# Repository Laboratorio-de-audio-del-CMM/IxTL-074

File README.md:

# IxTL-074

El IxTL-074 es un sintetizador DIY de frecuencia modulada (FM) desarrollado en el [Laboratorio de Experimentación Sonora del Centro Multimedia](https://www.instagram.com/labaudiocmm) entre agosto y octubre del 2026.

Su nombre proviene de un juego de palabras derivado del nombre de la fibra vegetal extraída de algunas especies de maguey (Ixtle[^1]) y uno de los componentes del sintetizador (el amplificador operacional TL-074). Busca trazar un paralelismo entre el tejido material de fibras vegetales y el sonido derivado de las interconexiones entre operadores de la síntesis FM.

## Funcionamiento
El IxTL-074 se compone de cuatro osciladores de onda cuadrada, cada uno con un rango de oscilación dedicado:

* **Oscilador 1:** 1.7 - 140 Hz aproximadamente
* **Oscilador 2:** 6.5 - 463 Hz aproximadamente
* **Oscilador 3:** 137 - 2266 Hz aproximadamente
* **Oscilador 4:** 147 - 5848 Hz aproximadamente

La frecuencia y amplitud de cada oscilador son determinadas por controles dedicados. La frecuencia puede ser variada mediante una señal moduladora [^2].

Cada oscilador cuenta con:
* **Tres salidas:**
    
    Correspondientes a la frecuencia y a la amplitud establecida con los controles dedicados. Cada salida puede funcionar como:
    * señal de audio, al conectarse a la mezcladora integrada
    * señal moduladora, al conectarse a las entradas de otro oscilador, o a su propia entrada

* **Tres entradas**

    Receptoras de señales moduladoras que derivarán en variaciones de frecuencia de las señales portadoras.

Cada oscilador tiene la capacidad de operar como señal portadora y moduladora simultaneamente.

Las conexiones entre salidas, entradas y mezcladora se establecen utilizando cables puente con puntas macho (también conocidos como "jumpers" o cables DuPont).

El sintetizador funciona con una fuente de alimentación de 9v con punta positiva.

La salida de audio integrada duplica una señal monofónica de audio (doble mono).

## Esquemático

## Documentación 
El repositorio posee tres archivos y dos carpetas de apoyo a la documentación:

1. Archivo [_**esquemático.pdf**_](esquemático.pdf)

    Diagrama esquemático de la versión 1.0.0 del sintetizador en formato _pdf_ para su consulta en alta resolución.
2. Archivo [_**lista-de-piezas-y-referencias.pdf**_](lista-de-piezas-y-referencias.pdf)

    Lista detallada de piezas, cantidades y su referencia en el esquemático y la serigrafía de la placa de circuito impreso.

3. Archivo [_**diseño.md**_](diseño.md)

    Descripción general del diseño electrónico del sintetizador para quien desee profundizar en su funcionamiento.

4. Carpeta [**proyecto-kicad**](proyecto-kicad)

    Archivos de diseño electrónico incluyendo esquemático (_.kicad_sch_), diseño de tarjeta de circuito impreso (_.kicad_pcb_) y proyecto (_.kicad_pro_).
   
5. Carpeta [**archivos-de-fabricacion**](archivos-de-fabricacion)

    Contiene los archivos gerber de diseño de tarjeta de circuito impreso usados para la fabricación de la placa.

## Licencia
En concordancia a los valores del conocimiento abierto, que promueven un acceso justo y equitativo a la información, la investigación y la producción de aprendizaje, el presente hardware se distribuye bajo la licencia **CERN Open Hardware Licence Version 2 - Strongly Reciprocal (CERN-OHL-S-2.0)**, con las siguientes implicaciones:

* **Libertad de uso y fabricación:** Tienes libertad para copiar, modificar y distribuir los archivos de diseño, así como para fabricar, ensamblar y vender productos físicos basados en ellos.
* **Reciprocidad fuerte (Copyleft fuerte):** Si modificas los archivos de diseño o distribuyes productos físicos creados a partir de ellos, estás obligado a liberar todo el diseño derivado bajo esta misma licencia (CERN-OHL-S v2).
* **Disponibilidad del código fuente:** Debes facilitar a los receptores el acceso al código fuente completo (archivos de diseño, esquemáticos, CAD) o indicar claramente la ubicación digital donde puedan descargarlo.
* **Atribución y registro de cambios:** Es obligatorio conservar los avisos de derechos de autor originales y añadir una nota indicando la fecha y una breve descripción de las modificaciones que hayas realizado.
* **Licencia de patentes:** Incluye una concesión de patentes perpetua y sin regalías para fabricar y vender el hardware. Esta concesión se revoca automáticamente si alguien inicia un litigio de patentes contra el proyecto.
* **Sin garantía:** El diseño y los objetos creados se proporcionan "tal cual" (*as is*), sin garantías de funcionamiento o comercialización, y sin responsabilidad legal para los creadores originales.

Para leer el texto legal completo y detallado, consulta el archivo [LICENCE](LICENCE) en este repositorio.

## Créditos

* #### Investigación, desarrollo, diseño de tarjeta de circuito impreso:
    [Francisco Ibrahim](https://www.instagram.com/mxxdbabgkqhkig9w0/) :shipit:, Colaborador del Laboratorio de Experimentación Sonora.
* #### Investigación, asesoramiento y supervisión del proyecto:
    Gonzalo T. Alonso, Jefe del Laboratorio de Experimentación Sonora.

### Agradecimientos
* [**Centro Multimedia**](https://cmm.cenart.gob.mx/) del Centro Nacional de las Artes.
* **Oscar Márquez y Rogelio Granados**, Servicio Social del Laboratorio de Experimentación Sonora. 
* **Juan Galindo**, Jefe del Laboratorio de Robótica y Sistemas Complejos.
* [**Proyecto KiCad**](https://www.kicad.org/) de software libre para la automatización del diseño electrónico.
* Productores cafetaleros de Veracruz y Chiapas.

## Documentación consultada
* Collins N. (2020). Handmade electronic music. New York: Routledge Taylor & Francis Group.
* Electro-Music. (s. f.). Simple 40106 oscillator with diode-based CV input [Archivo PDF]. https://electro-music.com/forum/phpbb-files/rmr_001__simple_40106_oscillator_with_diode_based_cv_input_905.pdf
* Evil Turtle Productions. (s. f.). Analog FM Drone/Kick Synth. https://www.evilturtle.nl/projects/fm-drone-synth
* Keim, R. (2020). Op-Amp Basics: Introduction to the Operational Amplifier. All About Circuits. https://www.allaboutcircuits.com/video-tutorials/op-amp-basics-introduction-to-the-operational-amplifier/
* Klein, M., & Erica Synths. (2021). mki x es.edu VCO manual [Archivo PDF]. Erica Synths.
* Lis A. (2022). 40106 dual oscillator. SFCS: Synthfox Custom Stuff. https://sfcs.neocities.org/module/SFP21/
* Williams, E. (2015). Logic noise: Sweet, sweet oscillator sounds. Hackaday. https://hackaday.com/2015/02/04/logic-noise-sweet-sweet-oscillator-sounds/

[^1]: Más información sobre el Ixtle y su uso en el Valle del Mezquital: https://tesiunamdocumentos.dgb.unam.mx/ptd2013/octubre/0702151/Index.html
[^2]: La modulación de frecuencia es un método de síntesis sonora. Consiste en variar (modular) la frecuencia de una señal (denominada portadora) con respecto a otra (denominada moduladora). El rango de la modulación de la frecuencia de la señal portadora será proporcional a la amplitud de la señal moduladora. La velocidad de la modulación de la frecuencia de la señal portadora será proporcional a la frecuencia de la señal moduladora.

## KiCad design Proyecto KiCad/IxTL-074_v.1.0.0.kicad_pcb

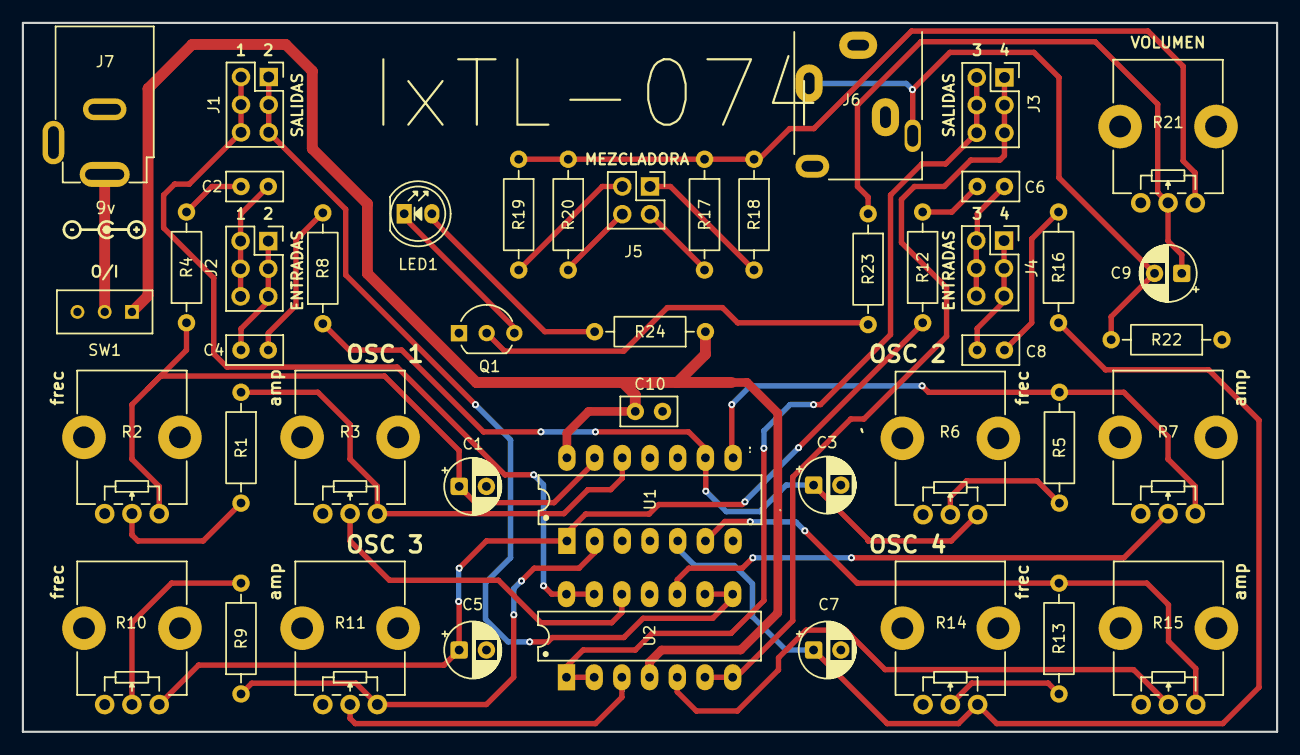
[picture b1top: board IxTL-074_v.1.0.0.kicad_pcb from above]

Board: 2 copper layers, 115.0 x 65.0 mm, 46 parts (0 on the bottom side), 41 nets.

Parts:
C1: 10µF; CP_Radial_D5.0mm_P2.50mm
C2, C4, C6, C8, C10: 100nF; C_Disc_D5.0mm_W2.5mm_P2.50mm
C3: 4.7µF; CP_Radial_D5.0mm_P2.50mm
C5, C9: 1µF; CP_Radial_D5.0mm_P2.50mm
C7: 0.22µF; CP_Radial_D5.0mm_P2.50mm
J1, J2, J3, J4: Pin Header 1x6 Female; PinSocket_2x03_P2.54mm_Vertical
J5: Pin Header Feamale 2x2; PinSocket_2x02_P2.54mm_Vertical
J6: SJ1-3515; jack-ixtl074
J7: Barrel Jack; Barrel_Jack_PTH_Slot
LED1: LED 5mm Azul; LED_D5.0mm
Q1: 2N3904; TO-92_Inline_Wide
R1, R4, R8, R12, R13, R16: 1k; R_Axial_DIN0207_L6.3mm_D2.5mm_P10.16mm_Horizontal
R2, R21: 100k; Potentiometer_Alps_RK09K_Single_Vertical
R3, R6, R7, R11, R14, R15: 50k; Potentiometer_Alps_RK09K_Single_Vertical
R5, R9, R24: 470; R_Axial_DIN0207_L6.3mm_D2.5mm_P10.16mm_Horizontal
R10: 10k; Potentiometer_Alps_RK09K_Single_Vertical
R17, R18, R19, R20: 10k; R_Axial_DIN0207_L6.3mm_D2.5mm_P10.16mm_Horizontal
R22, R23: 100k; R_Axial_DIN0207_L6.3mm_D2.5mm_P10.16mm_Horizontal
SW1: SPDT; 1P2T_SS-12D00_CNK
U1: CD40106BE; DIP-14_W7.62mm_LongPads
U2: TLC074CN; DIP-14_W7.62mm_LongPads

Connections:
+9V: C10.1, R24.1, SW1.1 (A), U1.14 (VDD), U2.4 (V+)
GND: C1.2, C3.2, C5.2, C7.2, C10.2, J6.1, J7.GND, Q1.1 (E), R3.1, R7.1, R11.1, R15.1, R21.1, R22.1, U1.3 (B), U1.7 (VSS), U1.11 (E), U2.11 (V-)
unnamed: C2.1, R4.2
unnamed: C2.2, J2.2, J2.4, J2.6
unnamed: C4.1, R8.2
unnamed: C4.2, J2.1, J2.3, J2.5
unnamed: C6.1, J4.2, J4.4, J4.6
unnamed: C6.2, R12.2
unnamed: C8.1, R16.2
unnamed: C8.2, J4.1, J4.3, J4.5
unnamed: C9.1, R21.2, R23.1
unnamed: C9.2, J6.2, J6.3, R22.2
unnamed: J5.1, R18.2
unnamed: J5.2, R19.2
unnamed: J5.3, R17.2
unnamed: J5.4, R20.2
unnamed: LED1.2 (A), R24.2
unnamed: LED1.1 (K), Q1.3 (C)
unnamed: Q1.2 (B), R23.2
unnamed: R1.2, R2.2
unnamed: R5.1, R6.2
unnamed: R9.2, R10.2
unnamed: R13.1, R14.2
unnamed: R17.1, R18.1, R19.1, R20.1, R21.3
unnamed: J7.PWR, SW1.2 (B)
unnamed: C5.1, R10.3, R12.1, U1.1 (A)
unnamed: C7.1, R14.3, R16.1, U1.5 (C)
unnamed: C3.1, R6.3, R8.1, U1.9 (D)
unnamed: C1.1, R2.3, R4.1, U1.13 (F)
unnamed: R9.1, R11.3, U1.2 (G=*A)
unnamed: R13.2, R15.3, U1.6 (I=*C)
unnamed: R5.2, R7.3, U1.8 (J=*D)
unnamed: R1.1, R3.3, U1.12 (L=*F)
unnamed: R11.2, U2.3 (+)
unnamed: J3.2, J3.4, J3.6, U2.1, U2.2 (-)
unnamed: R15.2, U2.5 (+)
unnamed: J3.1, J3.3, J3.5, U2.6 (-), U2.7
unnamed: R7.2, U2.10 (+)
unnamed: J1.1, J1.3, J1.5, U2.8, U2.9 (-)
unnamed: R3.2, U2.12 (+)
unnamed: J1.2, J1.4, J1.6, U2.13 (-), U2.14
